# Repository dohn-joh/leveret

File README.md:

# !!!WARNING!!!
Use these files at your own risk. I don't plan to write a build guide or bill of materials for these. These boards were prototypes for my own personal use. I will be releasing a unibody keyboard soon with a proper case, build guide, and silkscreen labels in a separate repo.

# MORE WARNINGS
- v1 is very challenging to build. I intentionally did not include the case files because this version is the earliest prototype with the most build complexity and flaws.
- Both v1 and v2 use reversible pcbs, and both versions lack informative silkscreen labels. If you're 100% decided on building this, then you'll need to reference the nets in the kicad files before soldering the mcu jumpers and socketing the mcu.

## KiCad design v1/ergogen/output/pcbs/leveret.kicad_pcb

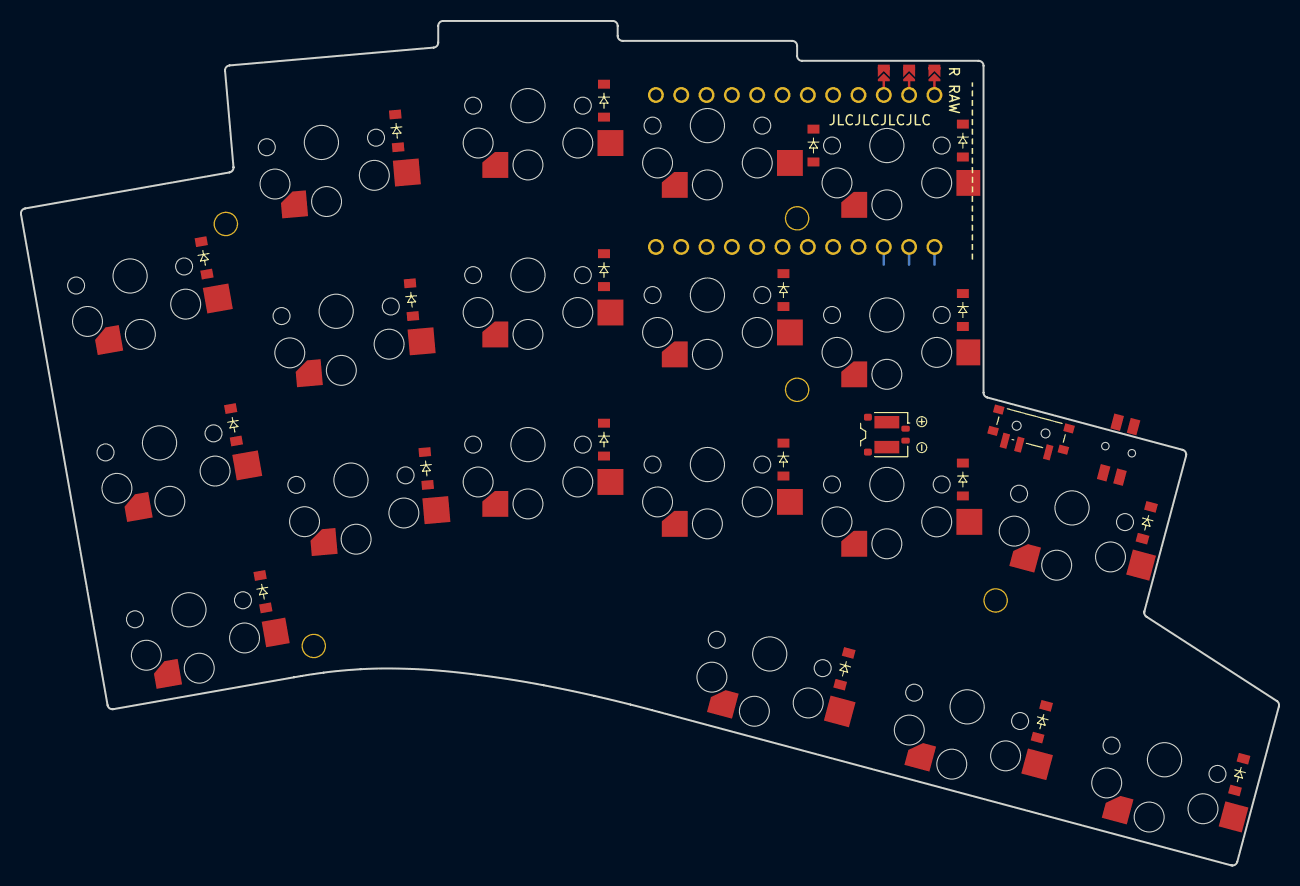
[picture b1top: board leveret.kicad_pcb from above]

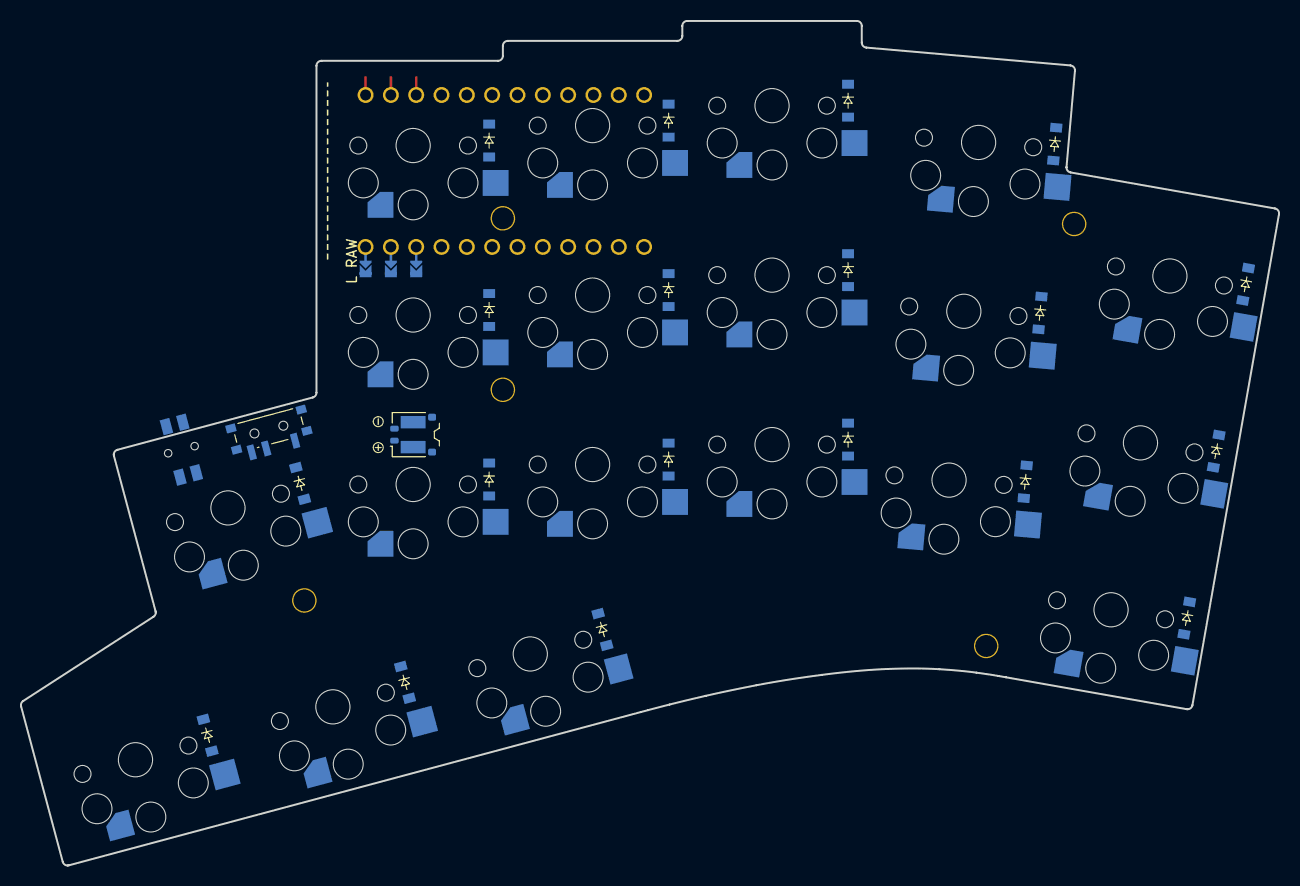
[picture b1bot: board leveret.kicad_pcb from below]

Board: 2 copper layers, 126.2 x 84.7 mm, 69 parts (19 on the bottom side), 34 nets, no tracks yet.

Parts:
CONN1: conn_molex_pico_ezmate_1x02
D1, D2, D3, D4, D5, D6, D7, D8, D9, D10, D11, D12, D13, D14, D15, D16, D17, D18, D19, D20, D21, D22, D23, D24, D25, D26, D27, D28, D29, D30, D31, D32, D33, D34, D35, D36, D37, D38: ComboDiode
H1, H2, H3, H4, H5: mounting_hole
ICON1: icon_bat
MCU1: ProMicro; nice_nano_v2_expanded
O1: leveret_edge_cuts
PAD1: pads
S1, S2, S3, S4, S5, S6, S7, S8, S9, S10, S11, S12, S13, S14, S15, S16, S17, S18, S19: PG1350
SW1: power_switch
SW2: reset_button; sw_reset_side

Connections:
BAT_P: CONN1.1, PAD1.1, PAD1.2, SW1.2, SW1.5
C1: MCU1.14, S12.1, S13.1, S19.1
C2: MCU1.15, S1.1, S2.1, S3.1
C3: MCU1.16, S4.1, S5.1, S6.1
C4: MCU1.17, S7.1, S8.1, S9.1
C5: MCU1.18, S10.1, S14.1, S15.1, S16.1
C6: MCU1.19, S11.1, S17.1
C7: MCU1.20, S18.1
GND: CONN1.2, MCU1.2, PAD1.1, PAD1.2, SW2.2, SW2.4
R1: D3.1, D6.1, D9.1, D12.1, D15.1, D22.1, D25.1, D28.1, D33.1, D38.1, MCU1.12
R2: D2.1, D5.1, D8.1, D11.1, D14.1, D21.1, D24.1, D27.1, D30.1, D32.1, MCU1.11
R3: D1.1, D4.1, D7.1, D10.1, D13.1, D18.1, D20.1, D23.1, D26.1, D29.1, D31.1, D36.1, MCU1.10
R4: D16.1, D17.1, D19.1, D34.1, D35.1, D37.1, MCU1.9
RAW: MCU1.1, SW1.3, SW1.6
RST: MCU1.3, SW2.1, SW2.3
base_lower: D17.2, D35.2, S11.2
base_upper: D18.2, D36.2, S17.2
extension_lower: D19.2, D37.2, S18.2
flexion_lower: D16.2, D34.2, S14.2
index_bottom: D10.2, D29.2, S7.2
index_home: D11.2, D30.2, S8.2
index_top: D12.2, D38.2, S9.2
inner_bottom: D13.2, D31.2, S10.2
inner_home: D14.2, D32.2, S15.2
inner_top: D15.2, D33.2, S16.2
middle_bottom: D7.2, D26.2, S4.2
middle_home: D8.2, D27.2, S5.2
middle_top: D9.2, D28.2, S6.2
pinky_bottom: D1.2, D20.2, S19.2
pinky_home: D2.2, D21.2, S12.2
pinky_top: D3.2, D22.2, S13.2
ring_bottom: D4.2, D23.2, S1.2
ring_home: D5.2, D24.2, S2.2
ring_top: D6.2, D25.2, S3.2

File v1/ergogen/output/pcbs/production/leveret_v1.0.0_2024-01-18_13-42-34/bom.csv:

Designator,Footprint,Quantity,Value,LCSC Part #
CONN1,conn_molex_pico_ezmate_1x02,1,,
"D1, D10, D11, D12, D13, D14, D15, D16, D17, D18, D19, D2, D20, D21, D22, D23, D24, D25, D26, D27, D28, D29, D3, D30, D31, D32, D33, D34, D35, D36, D37, D38, D4, D5, D6, D7, D8, D9",ComboDiode,38,,
"H1, H2, H3, H4, H5",mounting_hole,5,,
MCU1,nice_nano_v2_expanded,1,ProMicro,
O1,leveret_edge_cuts,1,leveret_edge_cuts,
PAD1,pads,1,,
SW,sw_reset_side,1,reset_button,
SW1,power_switch,1,,

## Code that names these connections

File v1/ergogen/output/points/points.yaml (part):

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        autobind: 10
        skip: false
        asym: both
        colrow: pinky_bottom
        name: matrix_pinky_bottom
        zone: *ref_0
        col: &ref_2
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        autobind: 10
        skip: false
        asym: both
        colrow: pinky_home
        name: matrix_pinky_home
        zone: *ref_0
        col: *ref_2
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        autobind: 10
        skip: false
        asym: both
        colrow: pinky_top
        name: matrix_pinky_top
        zone: *ref_0
        col: *ref_2
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
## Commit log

2024-05-20 init
2024-05-21 add readme
